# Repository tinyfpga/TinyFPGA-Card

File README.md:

# TinyFPGA-Card

A business card you can assemble into something neat.  See http://tinyfpga.com/card/ for details.

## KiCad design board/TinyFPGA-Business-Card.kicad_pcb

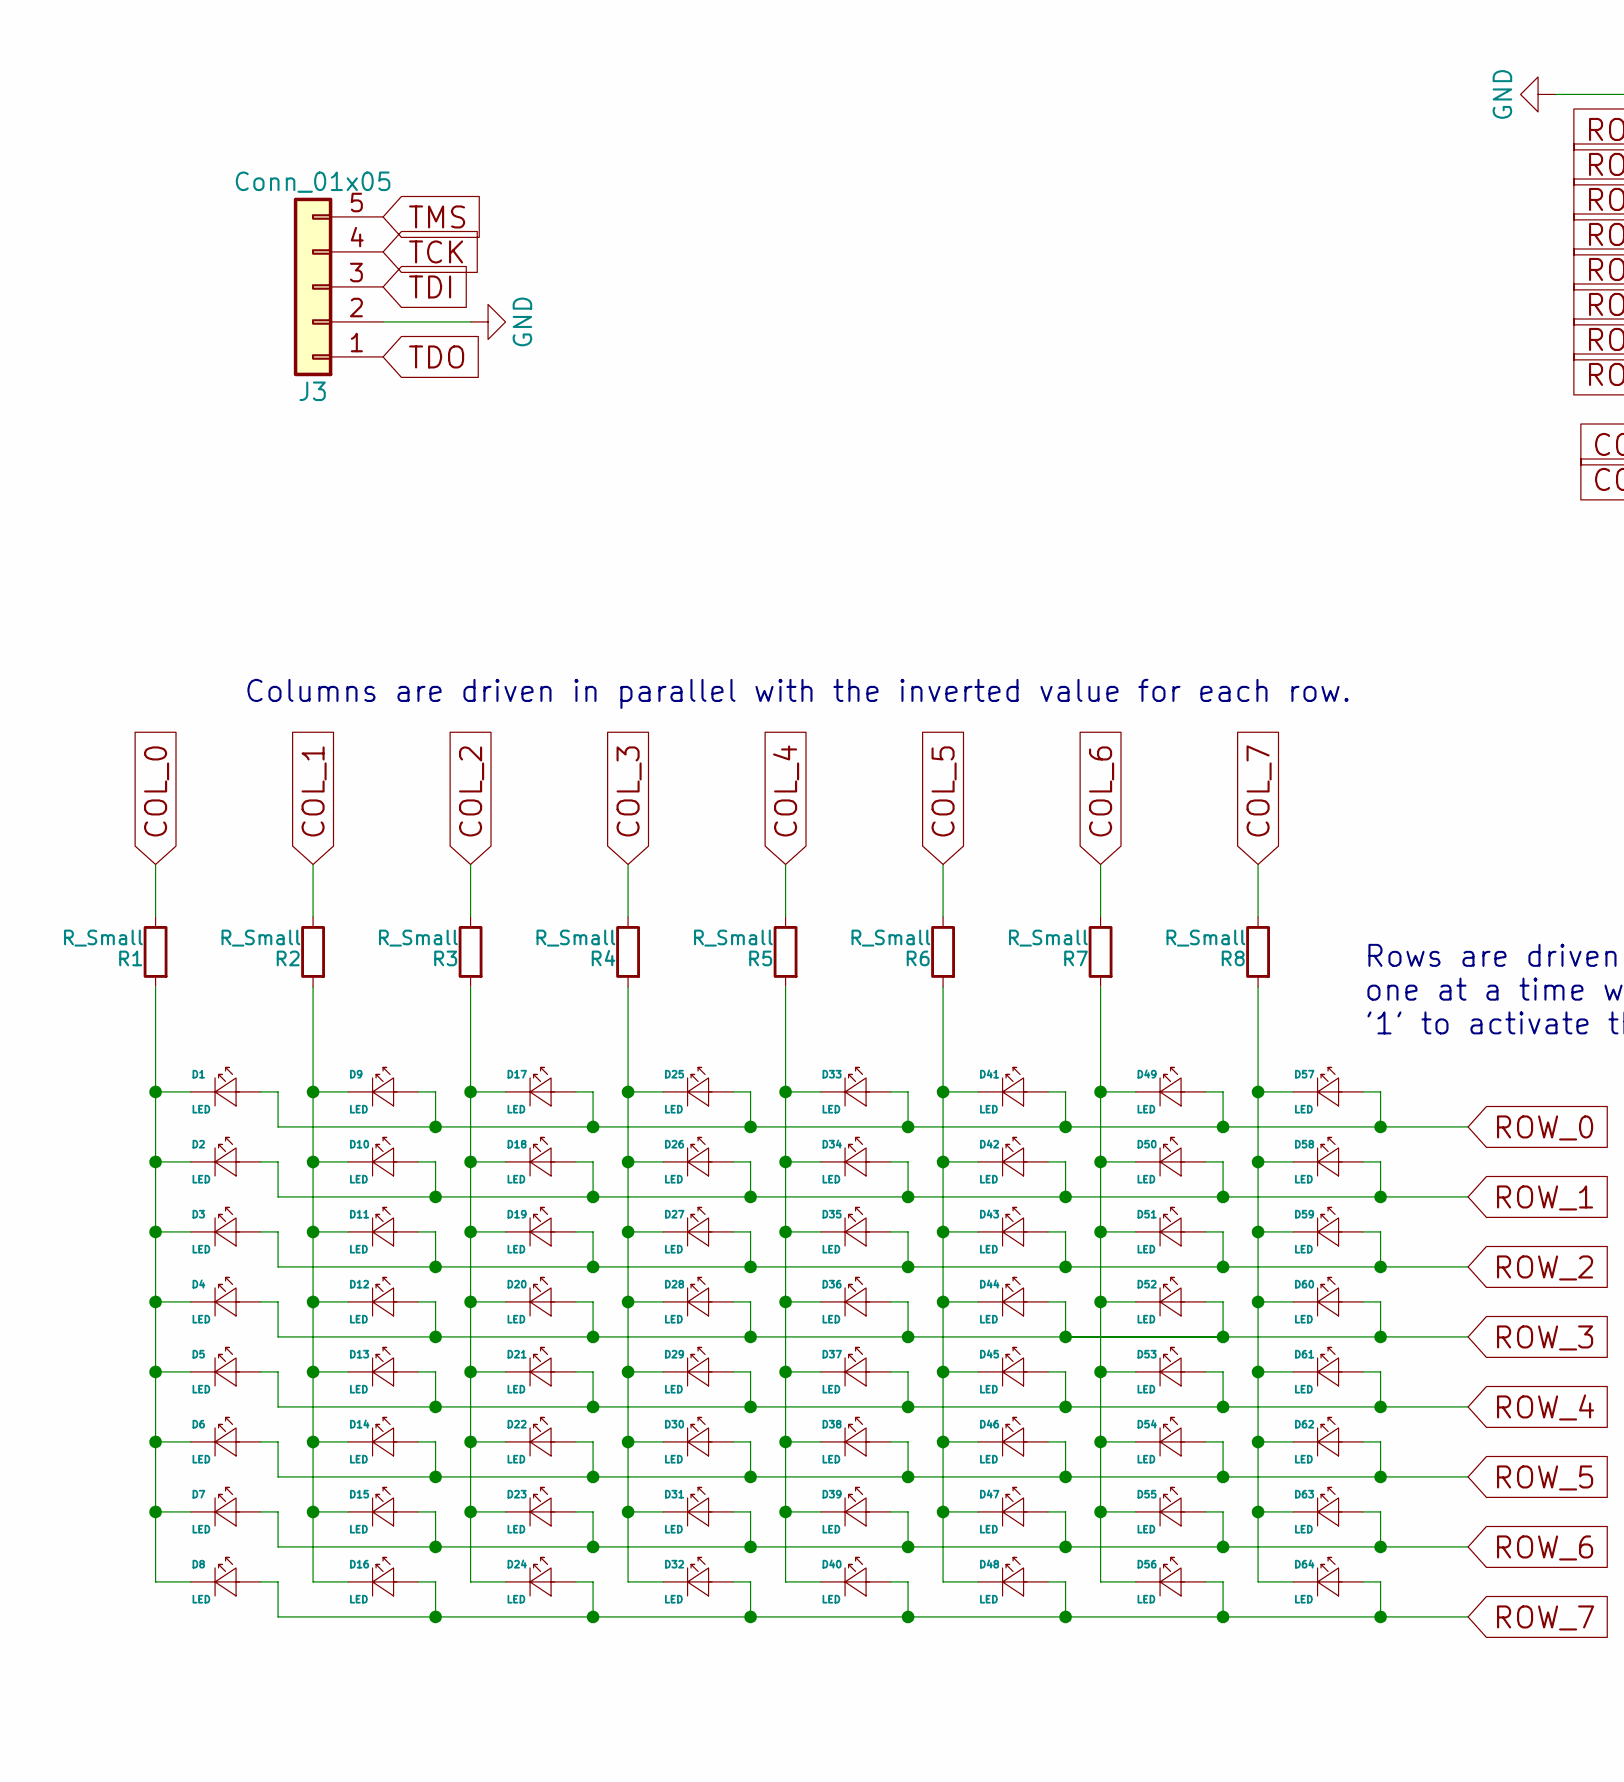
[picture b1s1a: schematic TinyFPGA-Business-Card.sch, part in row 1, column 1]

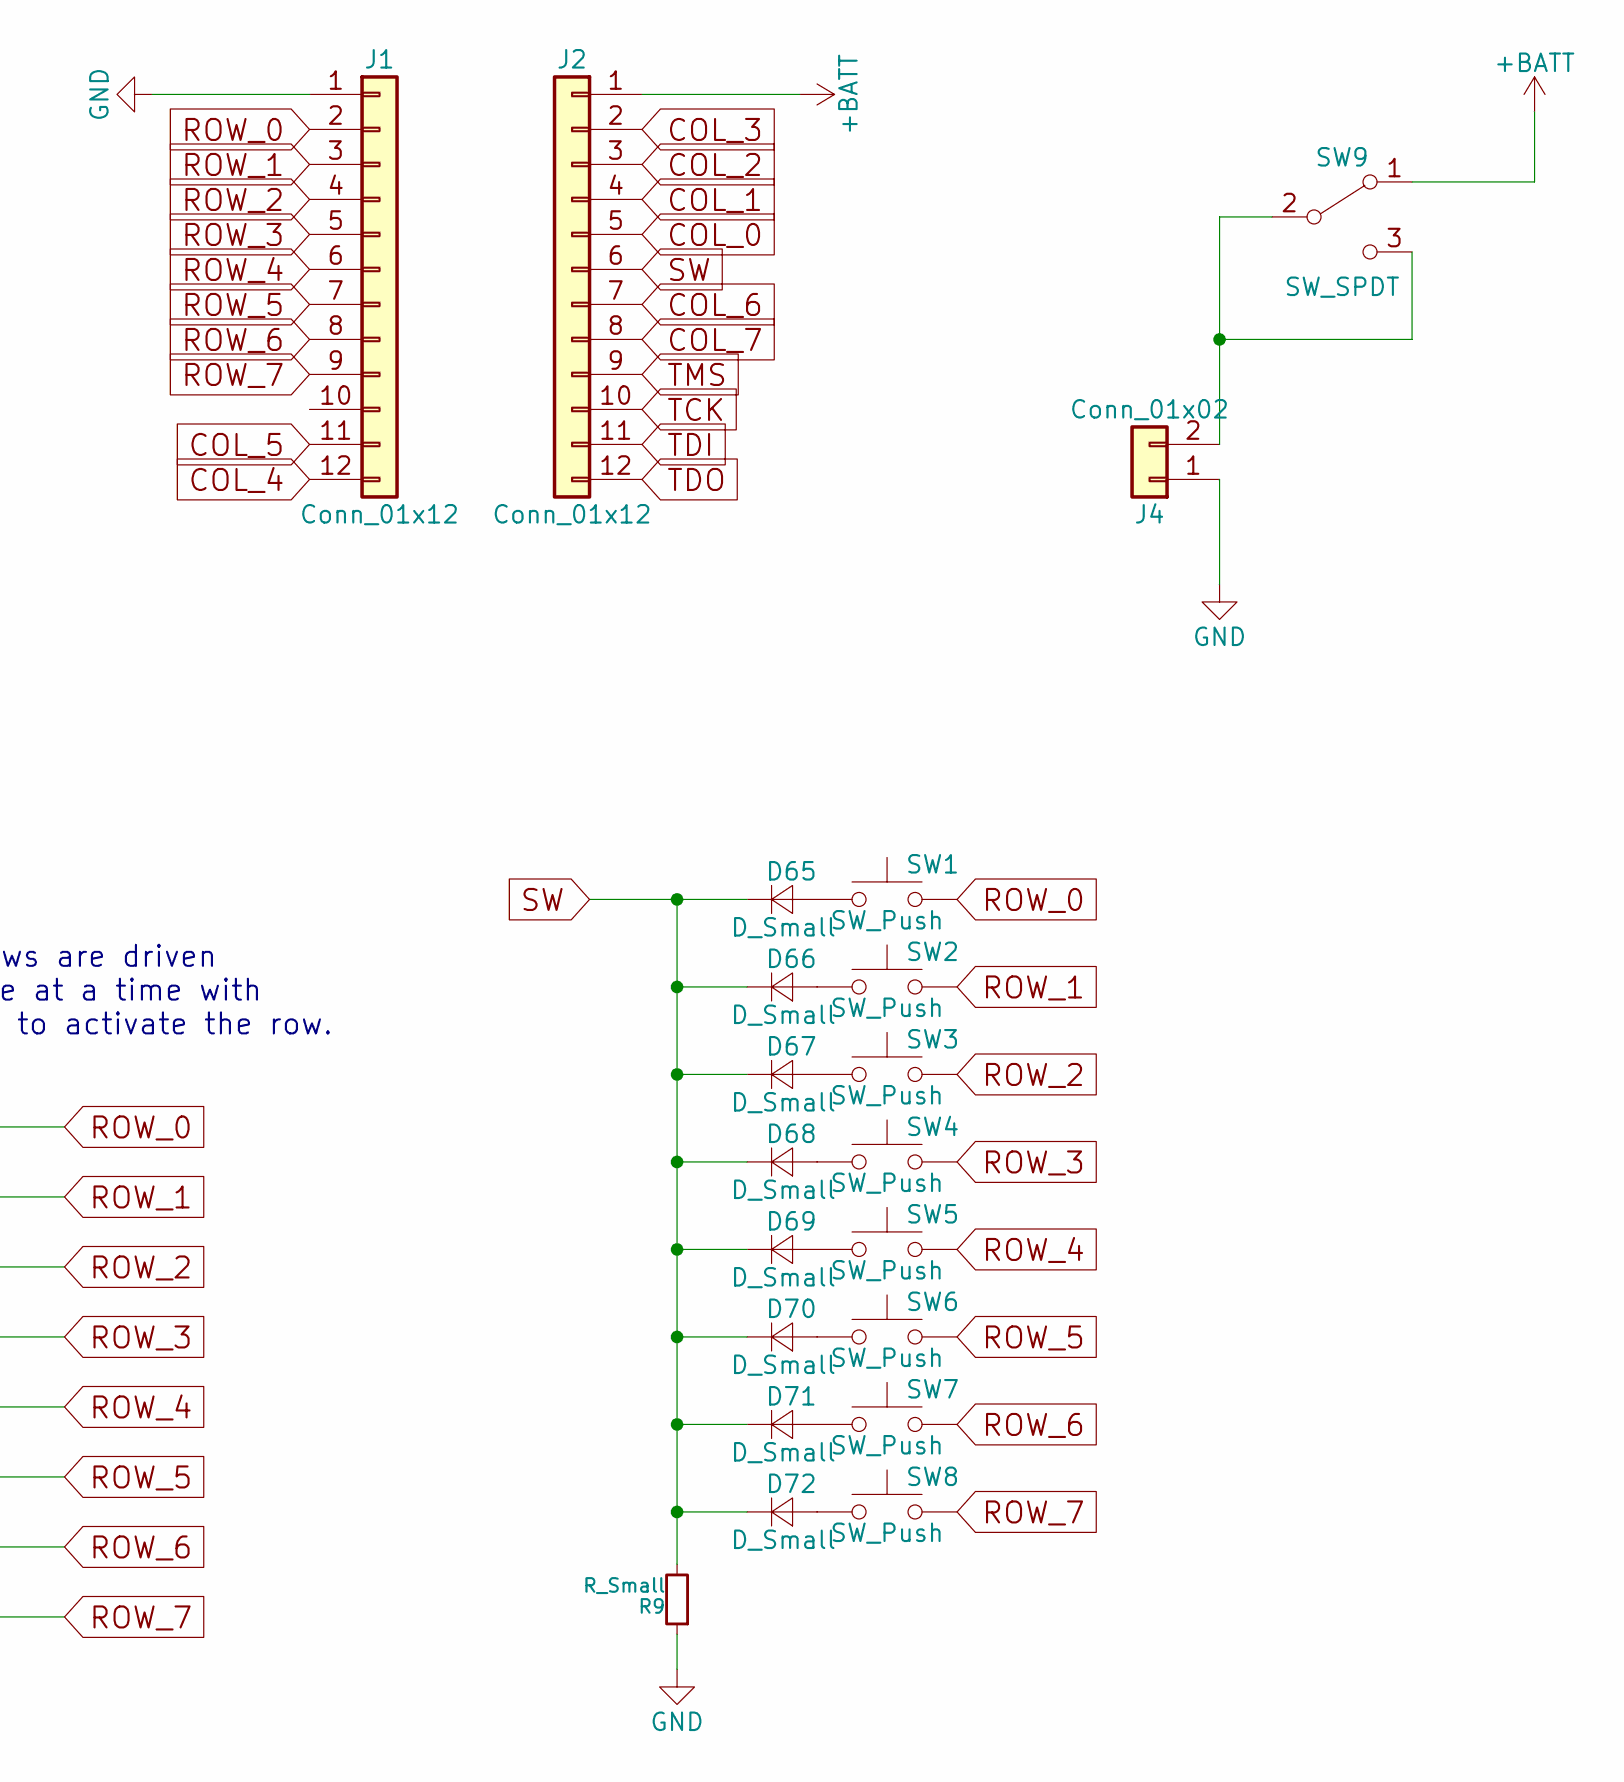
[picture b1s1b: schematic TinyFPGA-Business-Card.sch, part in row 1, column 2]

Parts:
D1, D2, D3, D4, D5, D6, D7, D8, D9, D10, D11, D12, D13, D14, D15, D16, D17, D18, D19, D20, D21, D22, D23, D24, D25, D26, D27, D28, D29, D30, D31, D32, D33, D34, D35, D36, D37, D38, D39, D40, D41, D42, D43, D44, D45, D46, D47, D48, D49, D50, D51, D52, D53, D54, D55, D56, D57, D58, D59, D60, D61, D62, D63, D64: LED; LED_0805_NOSILK
D65, D66, D67, D68, D69, D70, D71, D72: D_Small; D_0805
J1, J2: Conn_01x12
J3: Conn_01x05
J4: Conn_01x02
R1, R2, R3, R4, R5, R6, R7, R8, R9: R_Small; R_0805
SW1, SW2, SW3, SW4, SW5, SW6, SW7, SW8: SW_Push
SW9: SW_SPDT

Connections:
+BATT: J2.1, SW9.1 (A)
COL_0: J2.5, R1.2
COL_1: J2.4, R2.2
COL_2: J2.3, R3.2
COL_3: J2.2, R4.2
COL_4: J1.12, R5.2
COL_5: J1.11, R6.2
COL_6: J2.7, R7.2
COL_7: J2.8, R8.2
GND: J1.1, J3.2, J4.1, R9.1
unnamed: D1.1 (K), D2.1 (K), D3.1 (K), D4.1 (K), D5.1 (K), D6.1 (K), D7.1 (K), D8.1 (K), R1.1
unnamed: D9.1 (K), D10.1 (K), D11.1 (K), D12.1 (K), D13.1 (K), D14.1 (K), D15.1 (K), D16.1 (K), R2.1
unnamed: D17.1 (K), D18.1 (K), D19.1 (K), D20.1 (K), D21.1 (K), D22.1 (K), D23.1 (K), D24.1 (K), R3.1
unnamed: D25.1 (K), D26.1 (K), D27.1 (K), D28.1 (K), D29.1 (K), D30.1 (K), D31.1 (K), D32.1 (K), R4.1
unnamed: D33.1 (K), D34.1 (K), D35.1 (K), D36.1 (K), D37.1 (K), D38.1 (K), D39.1 (K), D40.1 (K), R5.1
unnamed: D41.1 (K), D42.1 (K), D43.1 (K), D44.1 (K), D45.1 (K), D46.1 (K), D47.1 (K), D48.1 (K), R6.1
unnamed: D49.1 (K), D50.1 (K), D51.1 (K), D52.1 (K), D53.1 (K), D54.1 (K), D55.1 (K), D56.1 (K), R7.1
unnamed: D57.1 (K), D58.1 (K), D59.1 (K), D60.1 (K), D61.1 (K), D62.1 (K), D63.1 (K), D64.1 (K), R8.1
unnamed: D65.2 (A), SW1.1
unnamed: D66.2 (A), SW2.1
unnamed: D67.2 (A), SW3.1
unnamed: D68.2 (A), SW4.1
unnamed: D69.2 (A), SW5.1
unnamed: D70.2 (A), SW6.1
unnamed: D71.2 (A), SW7.1
unnamed: D72.2 (A), SW8.1
unnamed: J4.2, SW9.2 (B), SW9.3 (C)
ROW_0: D1.2 (A), D9.2 (A), D17.2 (A), D25.2 (A), D33.2 (A), D41.2 (A), D49.2 (A), D57.2 (A), J1.2, SW1.2
ROW_1: D2.2 (A), D10.2 (A), D18.2 (A), D26.2 (A), D34.2 (A), D42.2 (A), D50.2 (A), D58.2 (A), J1.3, SW2.2
ROW_2: D3.2 (A), D11.2 (A), D19.2 (A), D27.2 (A), D35.2 (A), D43.2 (A), D51.2 (A), D59.2 (A), J1.4, SW3.2
ROW_3: D4.2 (A), D12.2 (A), D20.2 (A), D28.2 (A), D36.2 (A), D44.2 (A), D52.2 (A), D60.2 (A), J1.5, SW4.2
ROW_4: D5.2 (A), D13.2 (A), D21.2 (A), D29.2 (A), D37.2 (A), D45.2 (A), D53.2 (A), D61.2 (A), J1.6, SW5.2
ROW_5: D6.2 (A), D14.2 (A), D22.2 (A), D30.2 (A), D38.2 (A), D46.2 (A), D54.2 (A), D62.2 (A), J1.7, SW6.2
ROW_6: D7.2 (A), D15.2 (A), D23.2 (A), D31.2 (A), D39.2 (A), D47.2 (A), D55.2 (A), D63.2 (A), J1.8, SW7.2
ROW_7: D8.2 (A), D16.2 (A), D24.2 (A), D32.2 (A), D40.2 (A), D48.2 (A), D56.2 (A), D64.2 (A), J1.9, SW8.2
SW: D65.1 (K), D66.1 (K), D67.1 (K), D68.1 (K), D69.1 (K), D70.1 (K), D71.1 (K), D72.1 (K), J2.6, R9.2
TCK: J2.10, J3.4
TDI: J2.11, J3.3
TDO: J2.12, J3.1
TMS: J2.9, J3.5

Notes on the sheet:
Rows are driven one at a time with '1' to activate the row.
Columns are driven in parallel with the inverted value for each row.

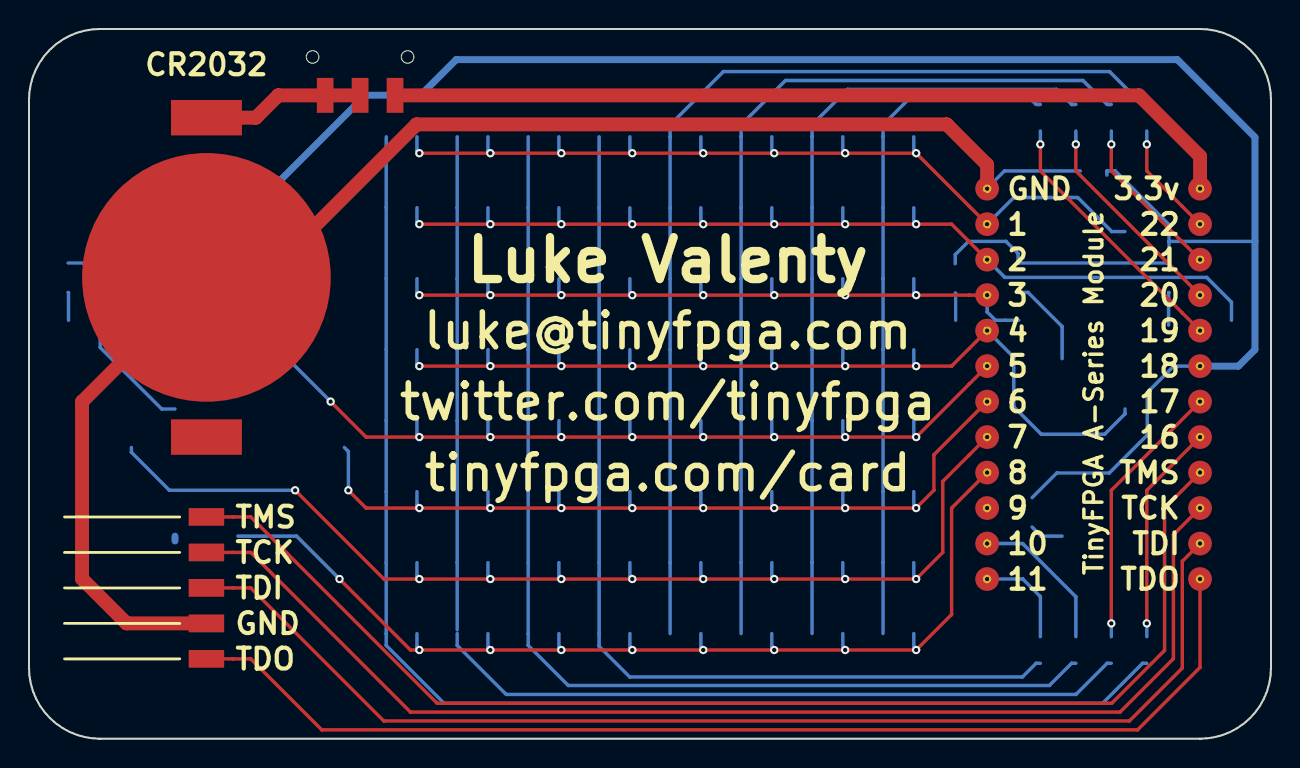
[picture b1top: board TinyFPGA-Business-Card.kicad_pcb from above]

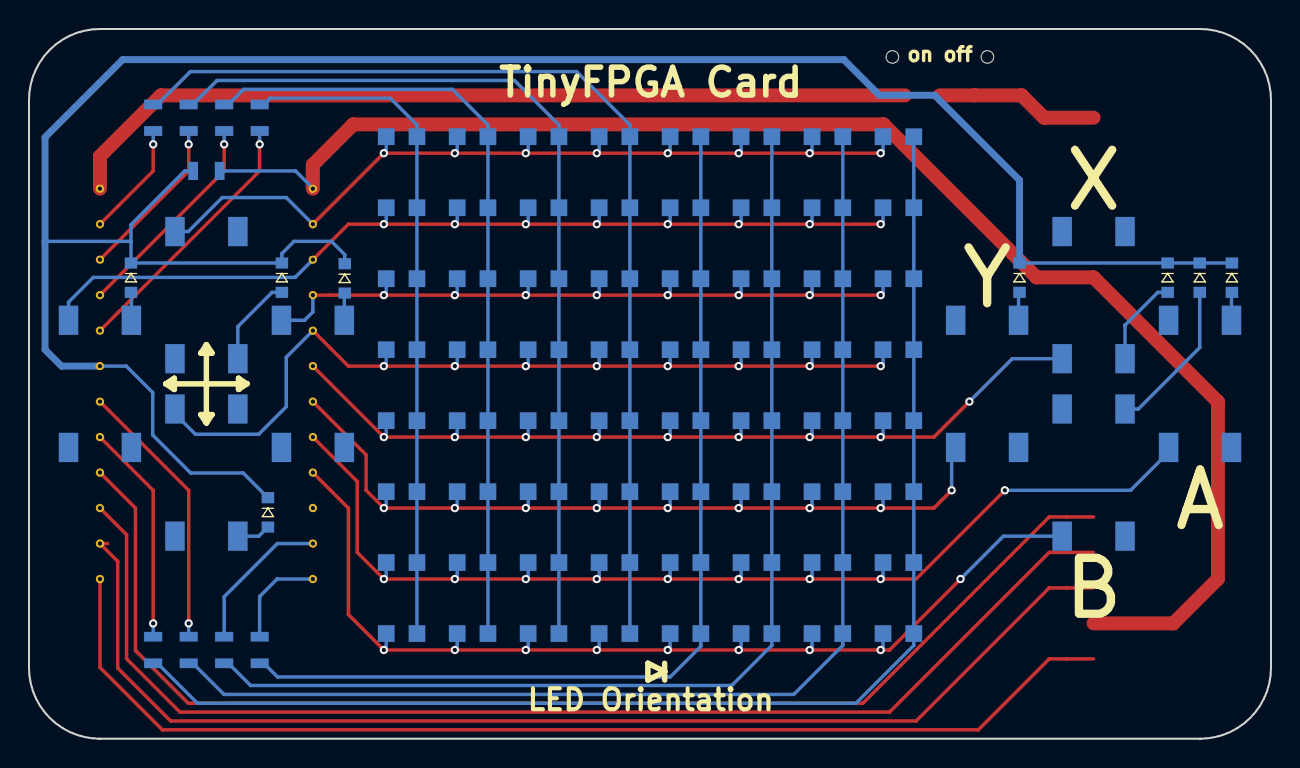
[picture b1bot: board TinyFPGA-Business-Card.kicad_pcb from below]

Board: 2 copper layers, 88.9 x 50.8 mm, 94 parts (89 on the bottom side), 40 nets.

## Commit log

2018-05-25 first commit of the TinyFPGA Business Card
